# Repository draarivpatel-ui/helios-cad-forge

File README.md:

# Helios-6 Parametric Solar Tracker & KiCad Telemetry Node

**Live CAD & EDA Workbench:** [https://aariv.me/helios-cad-forge/](https://aariv.me/helios-cad-forge/)

**Reference Design Note.** This repository provides a complete parametric CAD, KiCad schematic/PCB, BOM, and browser simulator reference design for a dual-axis solar tracker. Physical boards have not yet been fabricated or assembled.

Helios-6 is a parametric dual-axis solar tracker gimbal, OpenSCAD + watertight STL mesh generator, Spencer (1971) solar ephemeris calculator, and KiCad 8 RP2040 + INA219 telemetry node. The project pairs committed mechanical and electrical hardware artifacts (`cad/`, `pcb/`, `bom/`) with a zero-dependency in-browser CAD and EDA studio (`index.html`, `styles.css`, `engine.js`, `hardware.js`, `app.js`).

## Repository Architecture

```text
helios-cad-forge/
├── index.html                    # Dieter Rams / Mitutoyo blueprint light-mode CAD & EDA studio
├── styles.css                    # Drafting vellum (#F5F3EC) and anodized panel (#EAE6DA) stylesheet
├── engine.js                     # UMD solar position, worm-gear kinematics, watertight STL & OpenSCAD engine
├── hardware.js                   # UMD LCSC bill of materials, RP2040 + INA219 netlist & 80x56 mm PCB placement
├── app.js                        # Interactive 3D canvas viewport, stereographic sun-path & PCB inspector
├── cad/
│   ├── helios_gimbal.scad        # Parametric OpenSCAD source for the 6-body gimbal assembly
│   ├── helios_base.stl           # Watertight ASCII STL for the cylindrical stator base (genus 1)
│   ├── helios_worm_gear.stl      # Watertight ASCII STL for the 24-tooth involute worm wheel (genus 1)
│   └── helios_yoke.stl           # Watertight ASCII STL for the elevation U-yoke (genus 0)
├── pcb/
│   ├── helios_mppt_node.kicad_pro # KiCad 8 project configuration
│   ├── helios_mppt_node.kicad_sch # KiCad 8 schematic (48 placed symbols, full net labels & no-connects)
│   └── helios_mppt_node.kicad_pcb # KiCad 8 2-layer 80x56 mm PCB (48 non-overlapping footprints + GND zone)
├── bom/
│   └── bom.csv                   # 26-line grouped BOM (48 on-board parts + off-board steppers/LDRs/panel)
├── tools/
│   ├── build-artifacts.js        # Deterministic generator for cad/, pcb/, and bom/
│   ├── kicad.js                  # KiCad 8 S-expression schematic and PCB builder
│   ├── footprints.json           # Pad and courtyard geometry extracted from official KiCad 8 footprints
│   ├── sexpr.js                  # S-expression tokenizer and tree parser for test verification
│   └── verify-scad.mjs           # OpenSCAD WebAssembly volume and bounding-box parity verifier
└── tests/
    ├── engine.test.js            # Unit tests for solar math, gear kinematics, manifold topology & KiCad files
    └── dom-smoke.test.js         # DOM smoke tests for the interactive 3D workbench & anti-slop hygiene
```

## Core Engineering Capabilities

### 1. Spencer (1971) Solar Ephemeris & Meinel Clear-Sky Yield
* Computes fractional year, solar declination ($\delta$), equation of time (EoT), solar hour angle ($\omega$), solar zenith/elevation, and clockwise azimuth from true north.
* Integrates daily clear-sky beam irradiance using the Meinel air-mass attenuation model ($I_b = I_0 \cdot 0.7^{AM^{0.678}}$) to compare dual-axis tracking against fixed latitude tilt and horizontal surfaces.
* Renders an interactive polar stereographic sky dome with summer solstice (Day 172), equinox (Day 80), winter solstice (Day 355), and active day trajectories.

### 2. Self-Locking Worm-Gear Kinematics & Watertight Mesh Synthesis
* Synthesizes true involute tooth flanks ($\alpha = 20^\circ$ pressure angle, configurable module $m$ and tooth count $z$) with print-tolerance backlash compensation.
* Evaluates worm lead angle ($\lambda = \arctan(z_1 m / d_1)$) against static friction angle ($\phi_s = \arctan(\mu / \cos\alpha)$) to verify static self-locking under wind load without holding current.
* Builds 6 closed triangle meshes (`base`, `wheel`, `yoke`, `panel`, `pcb`, `sensors`) and validates every body with an Euler-Poincare manifold checker ($V - E + F = 2S - 2g$, zero boundary edges, zero non-manifold edges, consistent outward triangle winding).

### 3. RP2040 + INA219 Telemetry Node & Verified LCSC BOM
* Despite the `mppt` in the file names, the board has no MPPT converter. The INA219 measures panel current (across the `R14` shunt) and bus voltage; it does not track the maximum power point.
* Captures a 48-component on-board circuit (`U1` RP2040 QFN-56, `U2` W25Q16JVSSIQ QSPI flash, `U3` INA219AIDR high-side I2C current/voltage monitor, `U4` AP2112K-3.3 LDO, `Y1` 12 MHz crystal, `J1` USB-C, `R14` 0.1 ohm 1206 current shunt, quadrant LDR dividers `R9..R12`, and headers `J2..J8`).
* The 21 LCSC part numbers in `bom/bom.csv` were each matched to their manufacturer part number on lcsc.com on 2026-10-25. The BOM has no prices or total cost line yet.
* Every pin of all 48 placed components is verified against official KiCad 8 symbol definitions and either assigned to one of 40 named nets or explicitly documented in `NO_CONNECT`.
* All 48 footprint courtyards are placed on an 80 x 56 mm 2-layer board and verified by automated tests to lie strictly inside `Edge.Cuts` with zero courtyard overlaps.

## Verification & Local Commands

Requires Node.js 18+ (zero `npm` runtime dependencies):

```bash
# Run the 70-test unit and DOM smoke suite
npm test

# Deterministically regenerate all STL, OpenSCAD, KiCad 8, and BOM artifacts
npm run build
```

To run the optional OpenSCAD WebAssembly geometry parity check (`tools/verify-scad.mjs`):

```bash
npm install --no-save openscad-wasm-prebuilt
node tools/verify-scad.mjs
```

See [NOTES.md](NOTES.md) for full engineering notes and verification disclosures.

## License

Released under the [MIT License](LICENSE).

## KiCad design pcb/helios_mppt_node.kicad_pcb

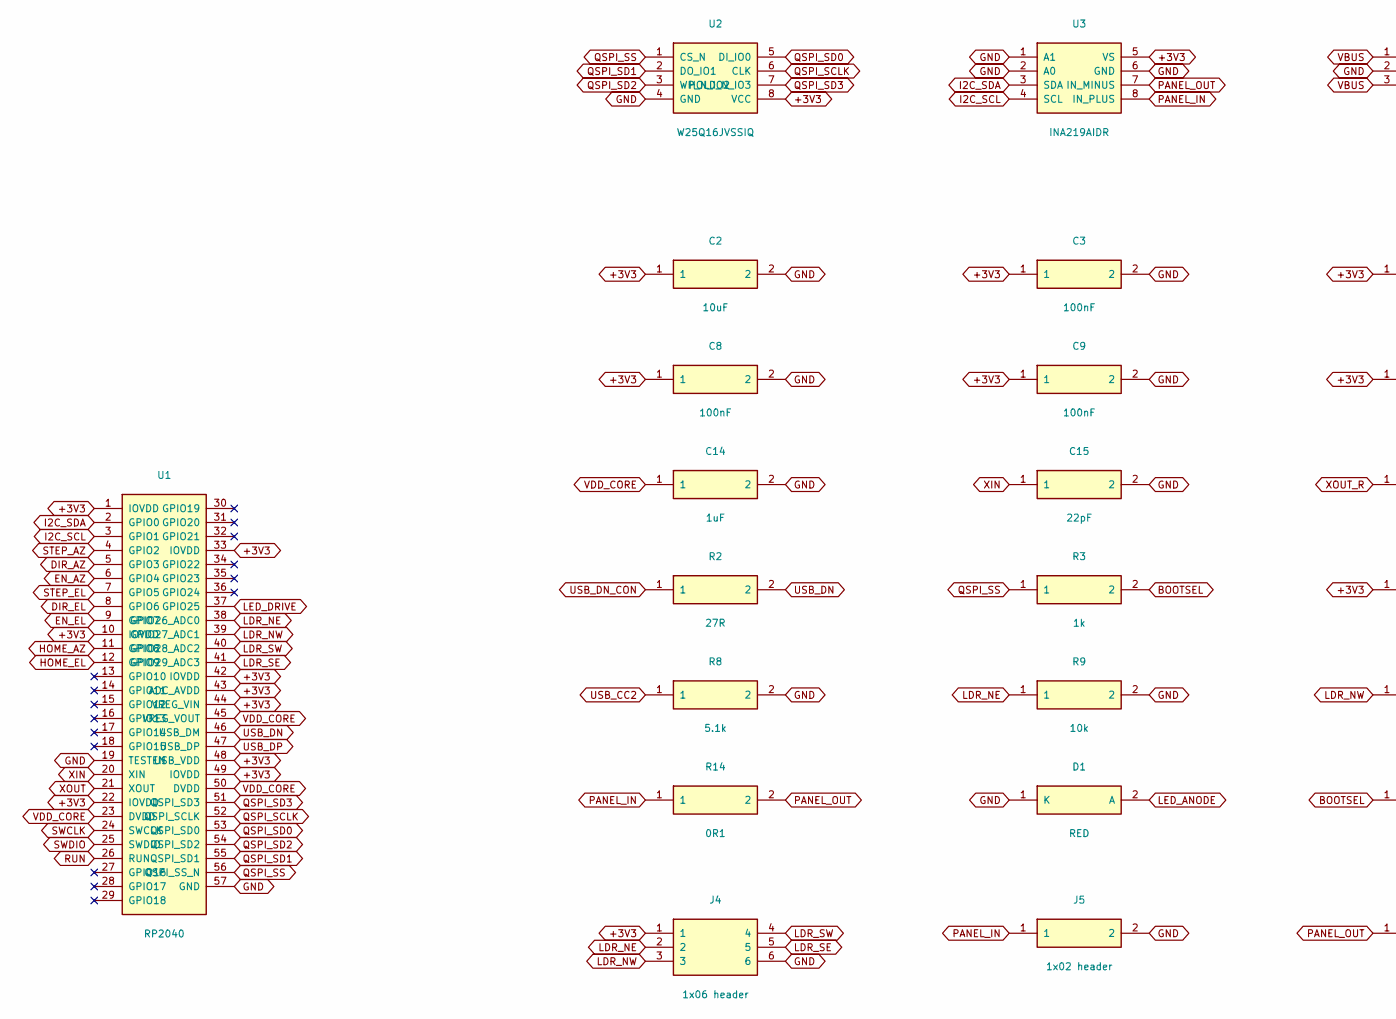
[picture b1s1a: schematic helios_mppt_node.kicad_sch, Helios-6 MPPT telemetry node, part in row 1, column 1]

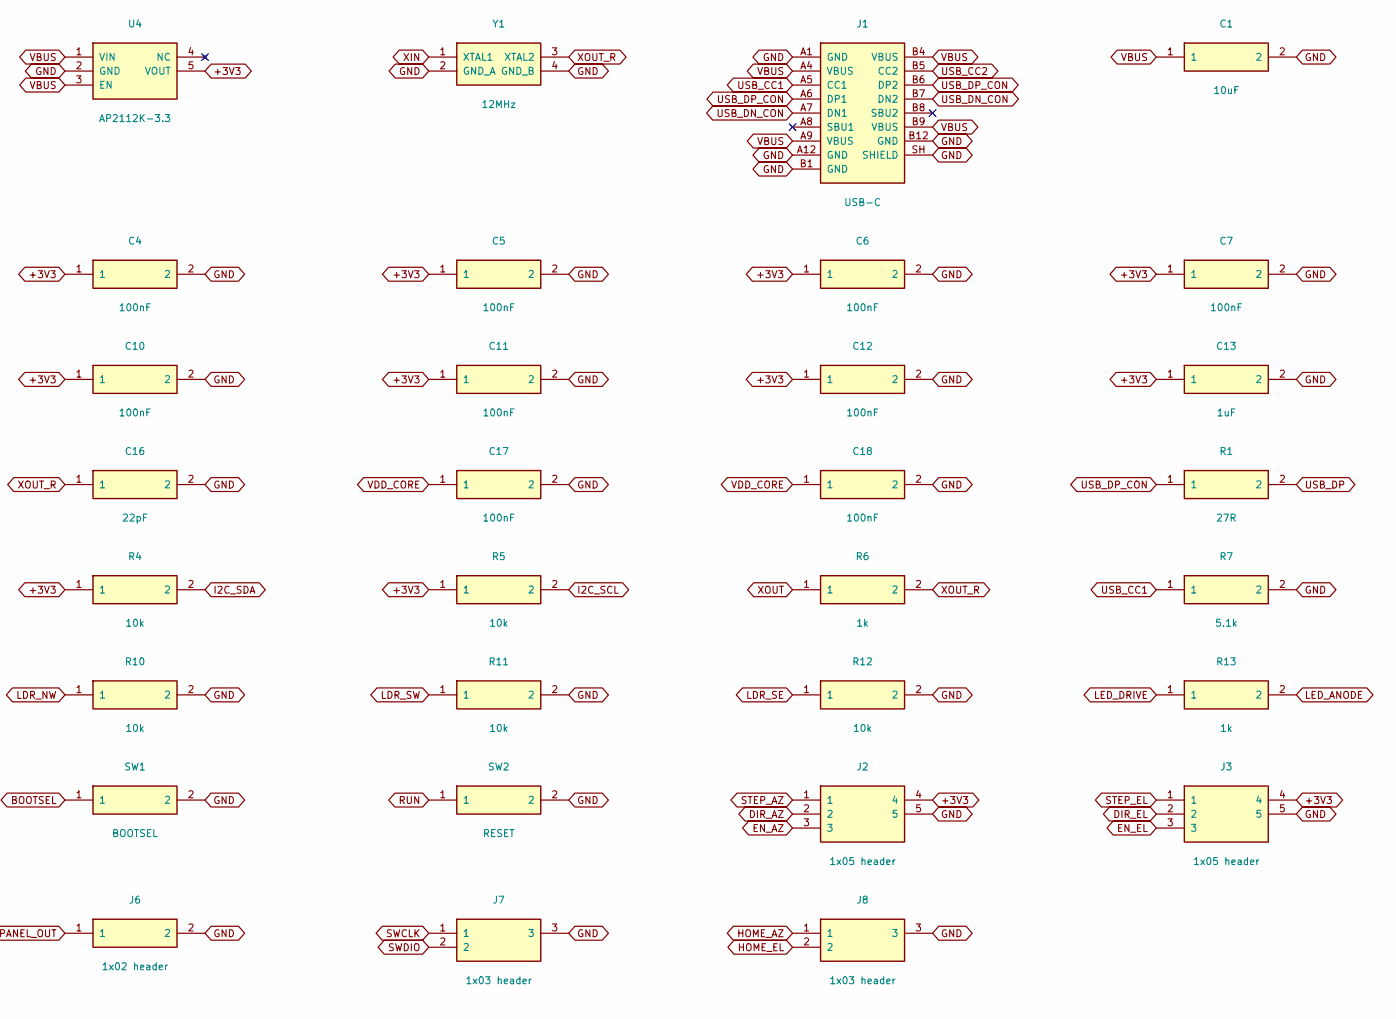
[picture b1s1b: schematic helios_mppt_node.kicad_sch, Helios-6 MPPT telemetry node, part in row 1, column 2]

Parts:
C1, C2: 10uF; C_0603_1608Metric; MPN CL10A106KP8NNNC; LCSC C19702
C3, C4, C5, C6, C7, C8, C9, C10, C11, C12, C17, C18: 100nF; C_0603_1608Metric; MPN CL10B104KB8NNNC; LCSC C1591
C13, C14: 1uF; C_0603_1608Metric; MPN CL10A105KB8NNNC; LCSC C15849
C15, C16: 22pF; C_0603_1608Metric; MPN CL10C220JB8NNNC; LCSC C1653
D1: RED; LED_0805_2012Metric; MPN NCD0805R1; LCSC C84256
J1: USB-C; USB_C_Receptacle_HRO_TYPE-C-31-M-12; MPN TYPE-C-31-M-12; LCSC C165948
J2, J3: 1x05 header; PinHeader_1x05_P2.54mm_Vertical; MPN B-2100S05P-A110; LCSC C124379
J4: 1x06 header; PinHeader_1x06_P2.54mm_Vertical; MPN B-2100S06P-A110; LCSC C124380
J5, J6: 1x02 header; PinHeader_1x02_P2.54mm_Vertical; MPN B-2100S02P-A110; LCSC C124375
J7, J8: 1x03 header; PinHeader_1x03_P2.54mm_Vertical; MPN B-2100S03P-A110; LCSC C124376
R1, R2: 27R; R_0603_1608Metric; MPN 0603WAF270JT5E; LCSC C25190
R3, R6, R13: 1k; R_0603_1608Metric; MPN 0603WAF1001T5E; LCSC C21190
R4, R5, R9, R10, R11, R12: 10k; R_0603_1608Metric; MPN 0603WAF1002T5E; LCSC C25804
R7, R8: 5.1k; R_0603_1608Metric; MPN 0603WAF5101T5E; LCSC C23186
R14: 0R1; R_1206_3216Metric; MPN 1206W4F100LT5E; LCSC C25334
SW1: BOOTSEL; SW_Push_1P1T_XKB_TS-1187A; MPN TS-1187A-B-A-B; LCSC C318884
SW2: RESET; SW_Push_1P1T_XKB_TS-1187A; MPN TS-1187A-B-A-B; LCSC C318884
U1: RP2040; QFN-56-1EP_7x7mm_P0.4mm_EP3.2x3.2mm; MPN RP2040; LCSC C2040
U2: W25Q16JVSSIQ; SOIC-8_5.3x5.3mm_P1.27mm; MPN W25Q16JVSSIQ; LCSC C82317
U3: INA219AIDR; SOIC-8_3.9x4.9mm_P1.27mm; MPN INA219AIDR; LCSC C138706
U4: AP2112K-3.3; SOT-23-5; MPN AP2112K-3.3TRG1; LCSC C51118
Y1: 12MHz; Crystal_SMD_3225-4Pin_3.2x2.5mm; MPN X322512MSB4SI; LCSC C9002

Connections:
+3V3: C2.1, C3.1, C4.1, C5.1, C6.1, C7.1, C8.1, C9.1, C10.1, C11.1, C12.1, C13.1, J2.4, J3.4, J4.1, R4.1, R5.1, U1.1 (IOVDD), U1.10 (IOVDD), U1.22 (IOVDD), U1.33 (IOVDD), U1.42 (IOVDD), U1.43 (ADC_AVDD), U1.44 (VREG_VIN), U1.48 (USB_VDD), U1.49 (IOVDD), U2.8 (VCC), U3.5 (VS), U4.5 (VOUT)
BOOTSEL: R3.2, SW1.1
DIR_AZ: J2.2, U1.5 (GPIO3)
DIR_EL: J3.2, U1.8 (GPIO6)
EN_AZ: J2.3, U1.6 (GPIO4)
EN_EL: J3.3, U1.9 (GPIO7)
GND: C1.2, C2.2, C3.2, C4.2, C5.2, C6.2, C7.2, C8.2, C9.2, C10.2, C11.2, C12.2, C13.2, C14.2, C15.2, C16.2, C17.2, C18.2, D1.1 (K), J1.A1 (GND), J1.A12 (GND), J1.B1 (GND), J1.B12 (GND), J1.SH (SHIELD), J2.5, J3.5, J4.6, J5.2, J6.2, J7.3, J8.3, R7.2, R8.2, R9.2, R10.2, R11.2, R12.2, SW1.2, SW2.2, U1.19 (TESTEN), U1.57 (GND), U2.4 (GND), U3.1 (A1), U3.2 (A0), U3.6 (GND), U4.2 (GND), Y1.2 (GND_A), Y1.4 (GND_B)
HOME_AZ: J8.1, U1.11 (GPIO8)
HOME_EL: J8.2, U1.12 (GPIO9)
I2C_SCL: R5.2, U1.3 (GPIO1), U3.4 (SCL)
I2C_SDA: R4.2, U1.2 (GPIO0), U3.3 (SDA)
LDR_NE: J4.2, R9.1, U1.38 (GPIO26_ADC0)
LDR_NW: J4.3, R10.1, U1.39 (GPIO27_ADC1)
LDR_SE: J4.5, R12.1, U1.41 (GPIO29_ADC3)
LDR_SW: J4.4, R11.1, U1.40 (GPIO28_ADC2)
LED_ANODE: D1.2 (A), R13.2
LED_DRIVE: R13.1, U1.37 (GPIO25)
PANEL_IN: J5.1, R14.1, U3.8 (IN_PLUS)
PANEL_OUT: J6.1, R14.2, U3.7 (IN_MINUS)
QSPI_SCLK: U1.52 (QSPI_SCLK), U2.6 (CLK)
QSPI_SD0: U1.53 (QSPI_SD0), U2.5 (DI_IO0)
QSPI_SD1: U1.55 (QSPI_SD1), U2.2 (DO_IO1)
QSPI_SD2: U1.54 (QSPI_SD2), U2.3 (WP_N_IO2)
QSPI_SD3: U1.51 (QSPI_SD3), U2.7 (HOLD_N_IO3)
QSPI_SS: R3.1, U1.56 (QSPI_SS_N), U2.1 (CS_N)
RUN: SW2.1, U1.26 (RUN)
STEP_AZ: J2.1, U1.4 (GPIO2)
STEP_EL: J3.1, U1.7 (GPIO5)
SWCLK: J7.1, U1.24 (SWCLK)
SWDIO: J7.2, U1.25 (SWDIO)
USB_CC1: J1.A5 (CC1), R7.1
USB_CC2: J1.B5 (CC2), R8.1
USB_DN: R2.2, U1.46 (USB_DM)
USB_DN_CON: J1.A7 (DN1), J1.B7 (DN2), R2.1
USB_DP: R1.2, U1.47 (USB_DP)
USB_DP_CON: J1.A6 (DP1), J1.B6 (DP2), R1.1
VBUS: C1.1, J1.A4 (VBUS), J1.A9 (VBUS), J1.B4 (VBUS), J1.B9 (VBUS), U4.1 (VIN), U4.3 (EN)
VDD_CORE: C14.1, C17.1, C18.1, U1.23 (DVDD), U1.45 (VREG_VOUT), U1.50 (DVDD)
XIN: C15.1, U1.20 (XIN), Y1.1 (XTAL1)
XOUT: R6.1, U1.21 (XOUT)
XOUT_R: C16.1, R6.2, Y1.3 (XTAL2)

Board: 2 copper layers, 48 parts (0 on the bottom side), 41 nets, no tracks yet.

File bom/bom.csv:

Reference,Qty,Value,Footprint,Manufacturer,MPN,LCSC,Mouser search,Description,Placement
C1 C2,2,10uF,Capacitor_SMD:C_0603_1608Metric,Samsung Electro-Mechanics,CL10A106KP8NNNC,C19702,https://www.mouser.com/c/?q=CL10A106KP8NNNC,10uF 10V X5R 0603,on board
C3 C4 C5 C6 C7 C8 C9 C10 C11 C12 C17 C18,12,100nF,Capacitor_SMD:C_0603_1608Metric,Samsung Electro-Mechanics,CL10B104KB8NNNC,C1591,https://www.mouser.com/c/?q=CL10B104KB8NNNC,100nF 50V X7R 0603,on board
C13 C14,2,1uF,Capacitor_SMD:C_0603_1608Metric,Samsung Electro-Mechanics,CL10A105KB8NNNC,C15849,https://www.mouser.com/c/?q=CL10A105KB8NNNC,1uF 50V X5R 0603,on board
C15 C16,2,22pF,Capacitor_SMD:C_0603_1608Metric,Samsung Electro-Mechanics,CL10C220JB8NNNC,C1653,https://www.mouser.com/c/?q=CL10C220JB8NNNC,22pF 50V C0G 0603,on board
D1,1,RED,LED_SMD:LED_0805_2012Metric,Nationstar,NCD0805R1,C84256,https://www.mouser.com/c/?q=NCD0805R1,"Red LED, 0805",on board
J1,1,USB-C,Connector_USB:USB_C_Receptacle_HRO_TYPE-C-31-M-12,Korean Hroparts Elec,TYPE-C-31-M-12,C165948,https://www.mouser.com/c/?q=TYPE-C-31-M-12,"USB Type-C receptacle, 16 position SMD",on board
J2 J3,2,1x05 header,Connector_PinHeader_2.54mm:PinHeader_1x05_P2.54mm_Vertical,Ckmtw,B-2100S05P-A110,C124379,https://www.mouser.com/c/?q=B-2100S05P-A110,"2.54 mm single-row pin header, 5 position",on board
J4,1,1x06 header,Connector_PinHeader_2.54mm:PinHeader_1x06_P2.54mm_Vertical,Ckmtw,B-2100S06P-A110,C124380,https://www.mouser.com/c/?q=B-2100S06P-A110,"2.54 mm single-row pin header, 6 position",on board
J5 J6,2,1x02 header,Connector_PinHeader_2.54mm:PinHeader_1x02_P2.54mm_Vertical,Ckmtw,B-2100S02P-A110,C124375,https://www.mouser.com/c/?q=B-2100S02P-A110,"2.54 mm single-row pin header, 2 position",on board
J7 J8,2,1x03 header,Connector_PinHeader_2.54mm:PinHeader_1x03_P2.54mm_Vertical,Ckmtw,B-2100S03P-A110,C124376,https://www.mouser.com/c/?q=B-2100S03P-A110,"2.54 mm single-row pin header, 3 position",on board
R1 R2,2,27R,Resistor_SMD:R_0603_1608Metric,UNI-ROYAL,0603WAF270JT5E,C25190,https://www.mouser.com/c/?q=0603WAF270JT5E,27 ohm 0603,on board
R3 R6 R13,3,1k,Resistor_SMD:R_0603_1608Metric,UNI-ROYAL,0603WAF1001T5E,C21190,https://www.mouser.com/c/?q=0603WAF1001T5E,1k 1% 0603,on board
R4 R5 R9 R10 R11 R12,6,10k,Resistor_SMD:R_0603_1608Metric,UNI-ROYAL,0603WAF1002T5E,C25804,https://www.mouser.com/c/?q=0603WAF1002T5E,10k 1% 0603,on board
R7 R8,2,5.1k,Resistor_SMD:R_0603_1608Metric,UNI-ROYAL,0603WAF5101T5E,C23186,https://www.mouser.com/c/?q=0603WAF5101T5E,5.1k 1% 0603,on board
R14,1,0R1,Resistor_SMD:R_1206_3216Metric,UNI-ROYAL,1206W4F100LT5E,C25334,https://www.mouser.com/c/?q=1206W4F100LT5E,0.1 ohm 1% 1206 shunt,on board
SW1,1,BOOTSEL,Button_Switch_SMD:SW_Push_1P1T_XKB_TS-1187A,XKB Connection,TS-1187A-B-A-B,C318884,https://www.mouser.com/c/?q=TS-1187A-B-A-B,"SMD tactile switch, 5.1 x 5.1 mm",on board
SW2,1,RESET,Button_Switch_SMD:SW_Push_1P1T_XKB_TS-1187A,XKB Connection,TS-1187A-B-A-B,C318884,https://www.mouser.com/c/?q=TS-1187A-B-A-B,"SMD tactile switch, 5.1 x 5.1 mm",on board
U1,1,RP2040,Package_DFN_QFN:QFN-56-1EP_7x7mm_P0.4mm_EP3.2x3.2mm,Raspberry Pi,RP2040,C2040,https://www.mouser.com/c/?q=RP2040,"Dual-core Cortex-M0+ microcontroller, QFN-56",on board
U2,1,W25Q16JVSSIQ,Package_SO:SOIC-8_5.3x5.3mm_P1.27mm,Winbond,W25Q16JVSSIQ,C82317,https://www.mouser.com/c/?q=W25Q16JVSSIQ,"16 Mbit QSPI flash, SOIC-8 208 mil",on board
U3,1,INA219AIDR,Package_SO:SOIC-8_3.9x4.9mm_P1.27mm,Texas Instruments,INA219AIDR,C138706,https://www.mouser.com/c/?q=INA219AIDR,"I2C current and bus voltage monitor, SOIC-8",on board
U4,1,AP2112K-3.3,Package_TO_SOT_SMD:SOT-23-5,Diodes Incorporated,AP2112K-3.3TRG1,C51118,https://www.mouser.com/c/?q=AP2112K-3.3TRG1,"3.3 V 600 mA LDO regulator, SOT-23-5",on board
Y1,1,12MHz,Crystal:Crystal_SMD_3225-4Pin_3.2x2.5mm,YXC,X322512MSB4SI,C9002,https://www.mouser.com/c/?q=X322512MSB4SI,"12 MHz 20 pF crystal, 3225 4-pad",on board
LDR1-LDR4,4,GL5528,off board,Senba Sensing,GL5528,,https://www.mouser.com/c/?q=GL5528,"CdS photoresistor, 5 mm, four on the sensor head via J4",off board
M1-M2,2,stepper,off board,,,,,"Two 200 step per revolution stepper motors, azimuth and elevation",off board
DRV1-DRV2,2,driver,off board,,,,,Two STEP/DIR/EN stepper driver modules wired to J2 and J3,off board
PV1,1,solar panel,off board,,,,,"Small solar panel on the elevation axis, wired to J5",off board
